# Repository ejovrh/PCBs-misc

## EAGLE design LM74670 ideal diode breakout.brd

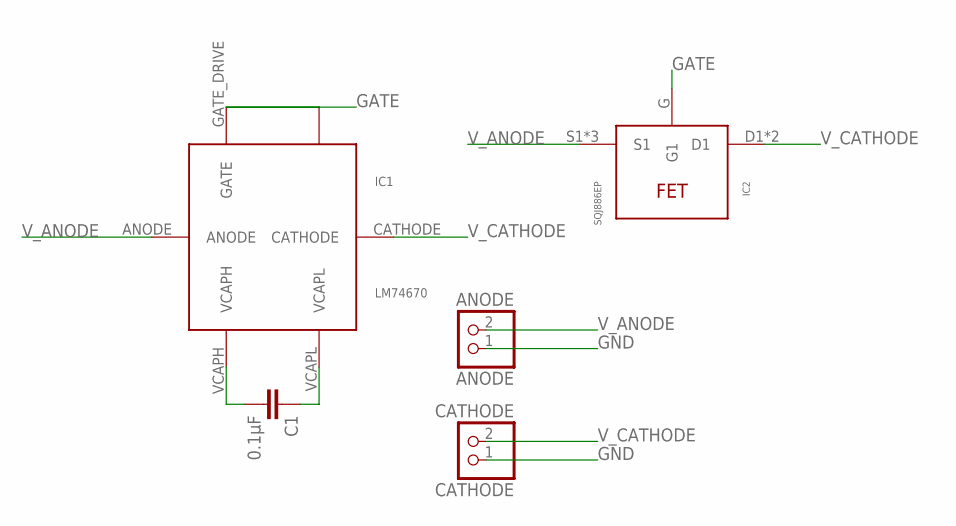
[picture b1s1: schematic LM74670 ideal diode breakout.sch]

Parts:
ANODE: ANODE; 1X02
C1: 0.1μF; C0805
CATHODE: CATHODE; 1X02
IC1: LM74670; VSSOP-8
IC2: SQJ886EP; SO-8L

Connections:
GATE: IC1.GATE_PULLD, IC2.G (G1)
GND: ANODE.1, CATHODE.1
unnamed: C1.2, IC1.VCAPH
unnamed: C1.1, IC1.VCAPL
V_ANODE: ANODE.2, IC1.ANODE, IC2.S1, IC2.S2 (S1), IC2.S3 (S1)
V_CATHODE: CATHODE.2, IC1.CATHODE, IC2.D1, IC2.D2 (D1)

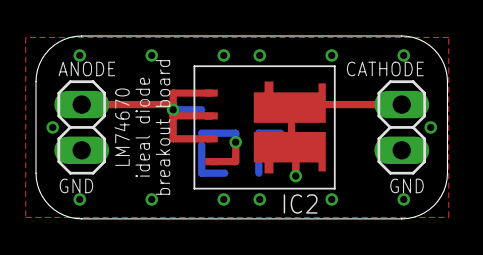
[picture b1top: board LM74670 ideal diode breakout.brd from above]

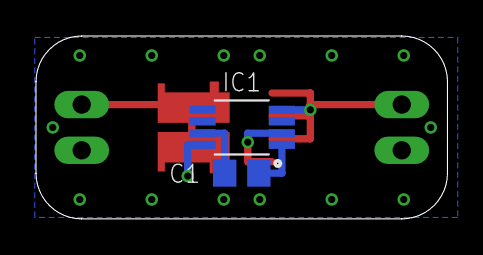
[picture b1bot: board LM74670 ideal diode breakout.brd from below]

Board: 2 copper layers, 22.9 x 10.2 mm, 5 parts (2 on the bottom side), 6 nets.

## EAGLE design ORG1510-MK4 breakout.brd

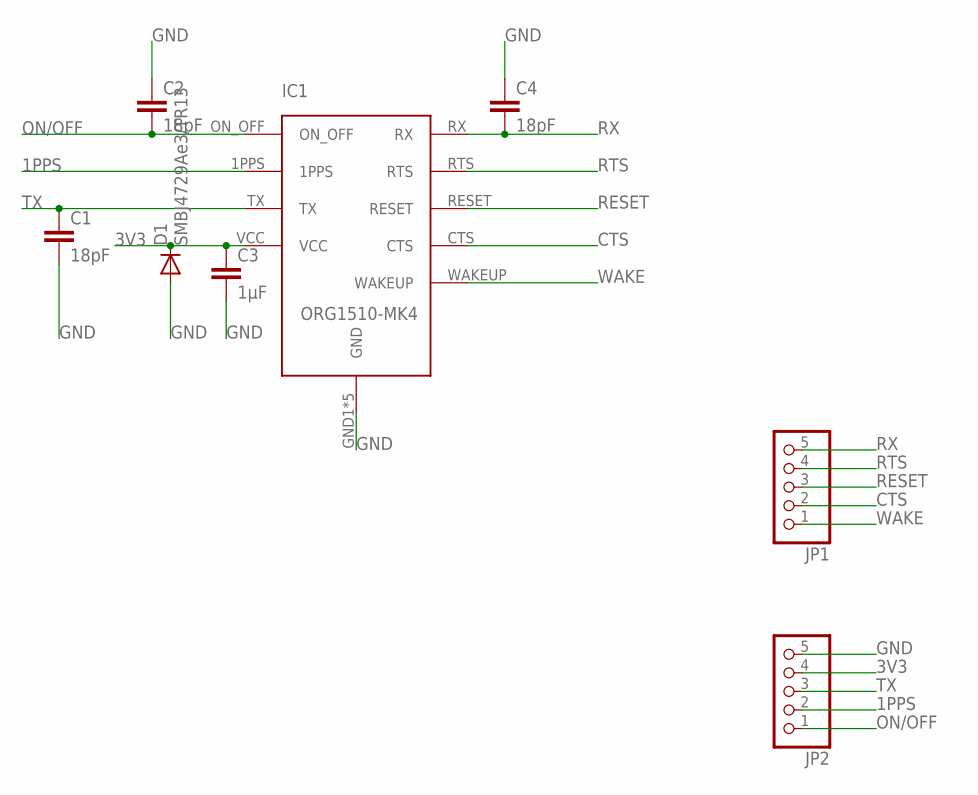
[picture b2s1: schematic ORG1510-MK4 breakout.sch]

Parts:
C1, C2, C4: 18pF; C0805
C3: 1µF; C0805
D1: SMBJ4729Ae3/TR13; DO214AA
IC1: ORG1510-MK4; PACKAGE
JP1, JP2: PINHD-1X5; 1X05

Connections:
1PPS: IC1.1PPS, JP2.2
3V3: C3.1, D1.C, IC1.VCC, JP2.4
CTS: IC1.CTS, JP1.2
GND: C1.2, C2.1, C3.2, C4.1, D1.A, IC1.GND1 (GND), IC1.GND2 (GND), IC1.GND3 (GND), IC1.GND4 (GND), IC1.GND5 (GND), JP2.5
ON/OFF: C2.2, IC1.ON_OFF, JP2.1
RESET: IC1.RESET, JP1.3
RTS: IC1.RTS, JP1.4
RX: C4.2, IC1.RX, JP1.5
TX: C1.1, IC1.TX, JP2.3
WAKE: IC1.WAKEUP, JP1.1

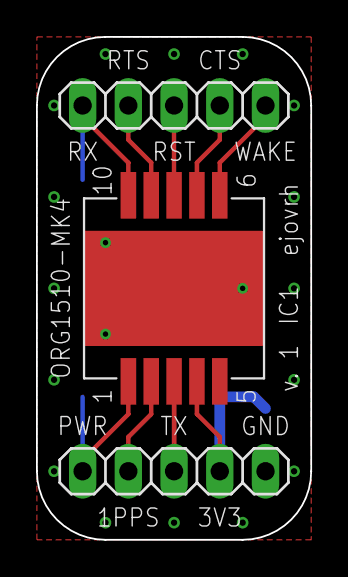
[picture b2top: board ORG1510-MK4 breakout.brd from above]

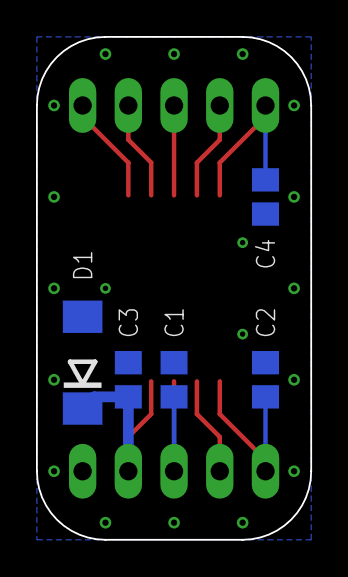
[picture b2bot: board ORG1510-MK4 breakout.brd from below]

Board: 2 copper layers, 15.2 x 27.9 mm, 8 parts (5 on the bottom side), 10 nets.

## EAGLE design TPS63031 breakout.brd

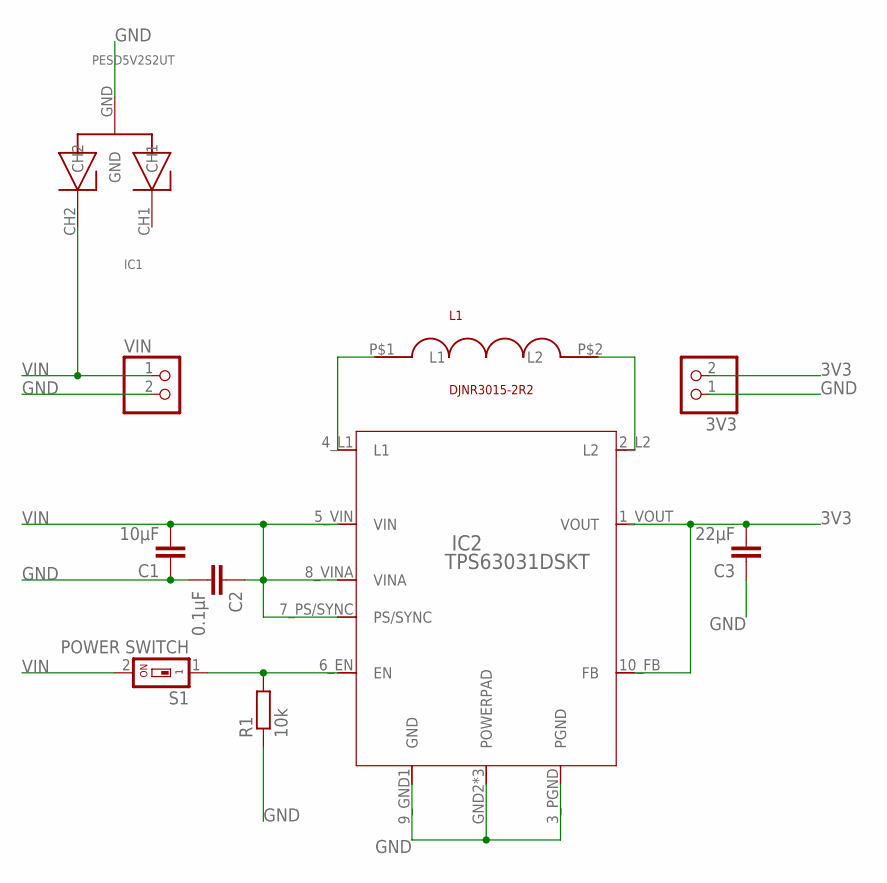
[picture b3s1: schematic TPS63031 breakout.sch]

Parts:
3V3: PINHD-1X2; 1X02
C1: 10µF; C0805
C2: 0.1µF; C0805
C3: 22µF; C0805
IC1: PESD5V2S2UT; SOT-23
IC2: TPS63031DSKT; SMT
L1: DJNR3015-2R2; FFF
R1: 10k; R0805
S1: POWER SWITCH; SMS-001
VIN: PINHD-1X2; 1X02

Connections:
3V3: 3V3.2, C3.2, IC2.1_VOUT (VOUT), IC2.10_FB (FB)
GND: 3V3.1, C1.1, C2.2, C3.1, IC1.GND, IC2.3_PGND (PGND), IC2.9_GND1 (GND), IC2.GND2 (POWERPAD), IC2.GND3 (POWERPAD), IC2.GND4 (POWERPAD), R1.1, VIN.2
L1: IC2.4_L1 (L1), L1.P$1 (L1)
L2: IC2.2_L2 (L2), L1.P$2 (L2)
unnamed: IC2.6_EN (EN), R1.2, S1.1
VIN: C1.2, C2.1, IC1.CH2, IC2.5_VIN (VIN), IC2.7_PS/SYNC (PS/SYNC), IC2.8_VINA (VINA), S1.2, VIN.1

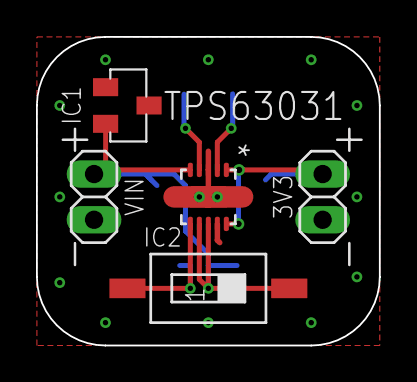
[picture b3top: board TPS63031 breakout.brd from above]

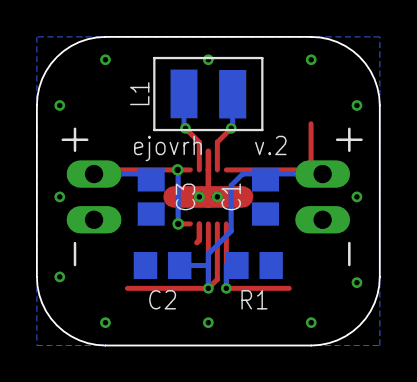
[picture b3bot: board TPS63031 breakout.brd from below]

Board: 2 copper layers, 19.1 x 17.1 mm, 10 parts (5 on the bottom side), 6 nets.
